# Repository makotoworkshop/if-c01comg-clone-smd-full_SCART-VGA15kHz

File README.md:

IF-C01COMG Clone board SMD Full size_SCART-VGA15kHz

This is a full sized version of the IF-C01COMG board for JVC pro monitors (TM-Hxx50CG) and some others...

It's basically the THT base board I made some months ago, with most components changed to SMD.

Credit goes to James Vanderloeff for the dual input idea.

Board is for now completely untested...

Finally this is a Kicad 5.1 project :D

You're welcome to clone, sell, re-design and whatever, see LICENSE.

(2021) Martin Hejnfelt (martin@hejnfelt.com)
This work is free. You can redistribute it and/or modify it under the
terms of the Do What The Fuck You Want To Public License, Version 2,
as published by Sam Hocevar. See the LICENSE file for more details.

—————————————————————————————

edit (2024) makotoworkshop.org

For more informations, see https://burogu.makotoworkshop.org/index.php?post/2024/08/08/jvc-rgb

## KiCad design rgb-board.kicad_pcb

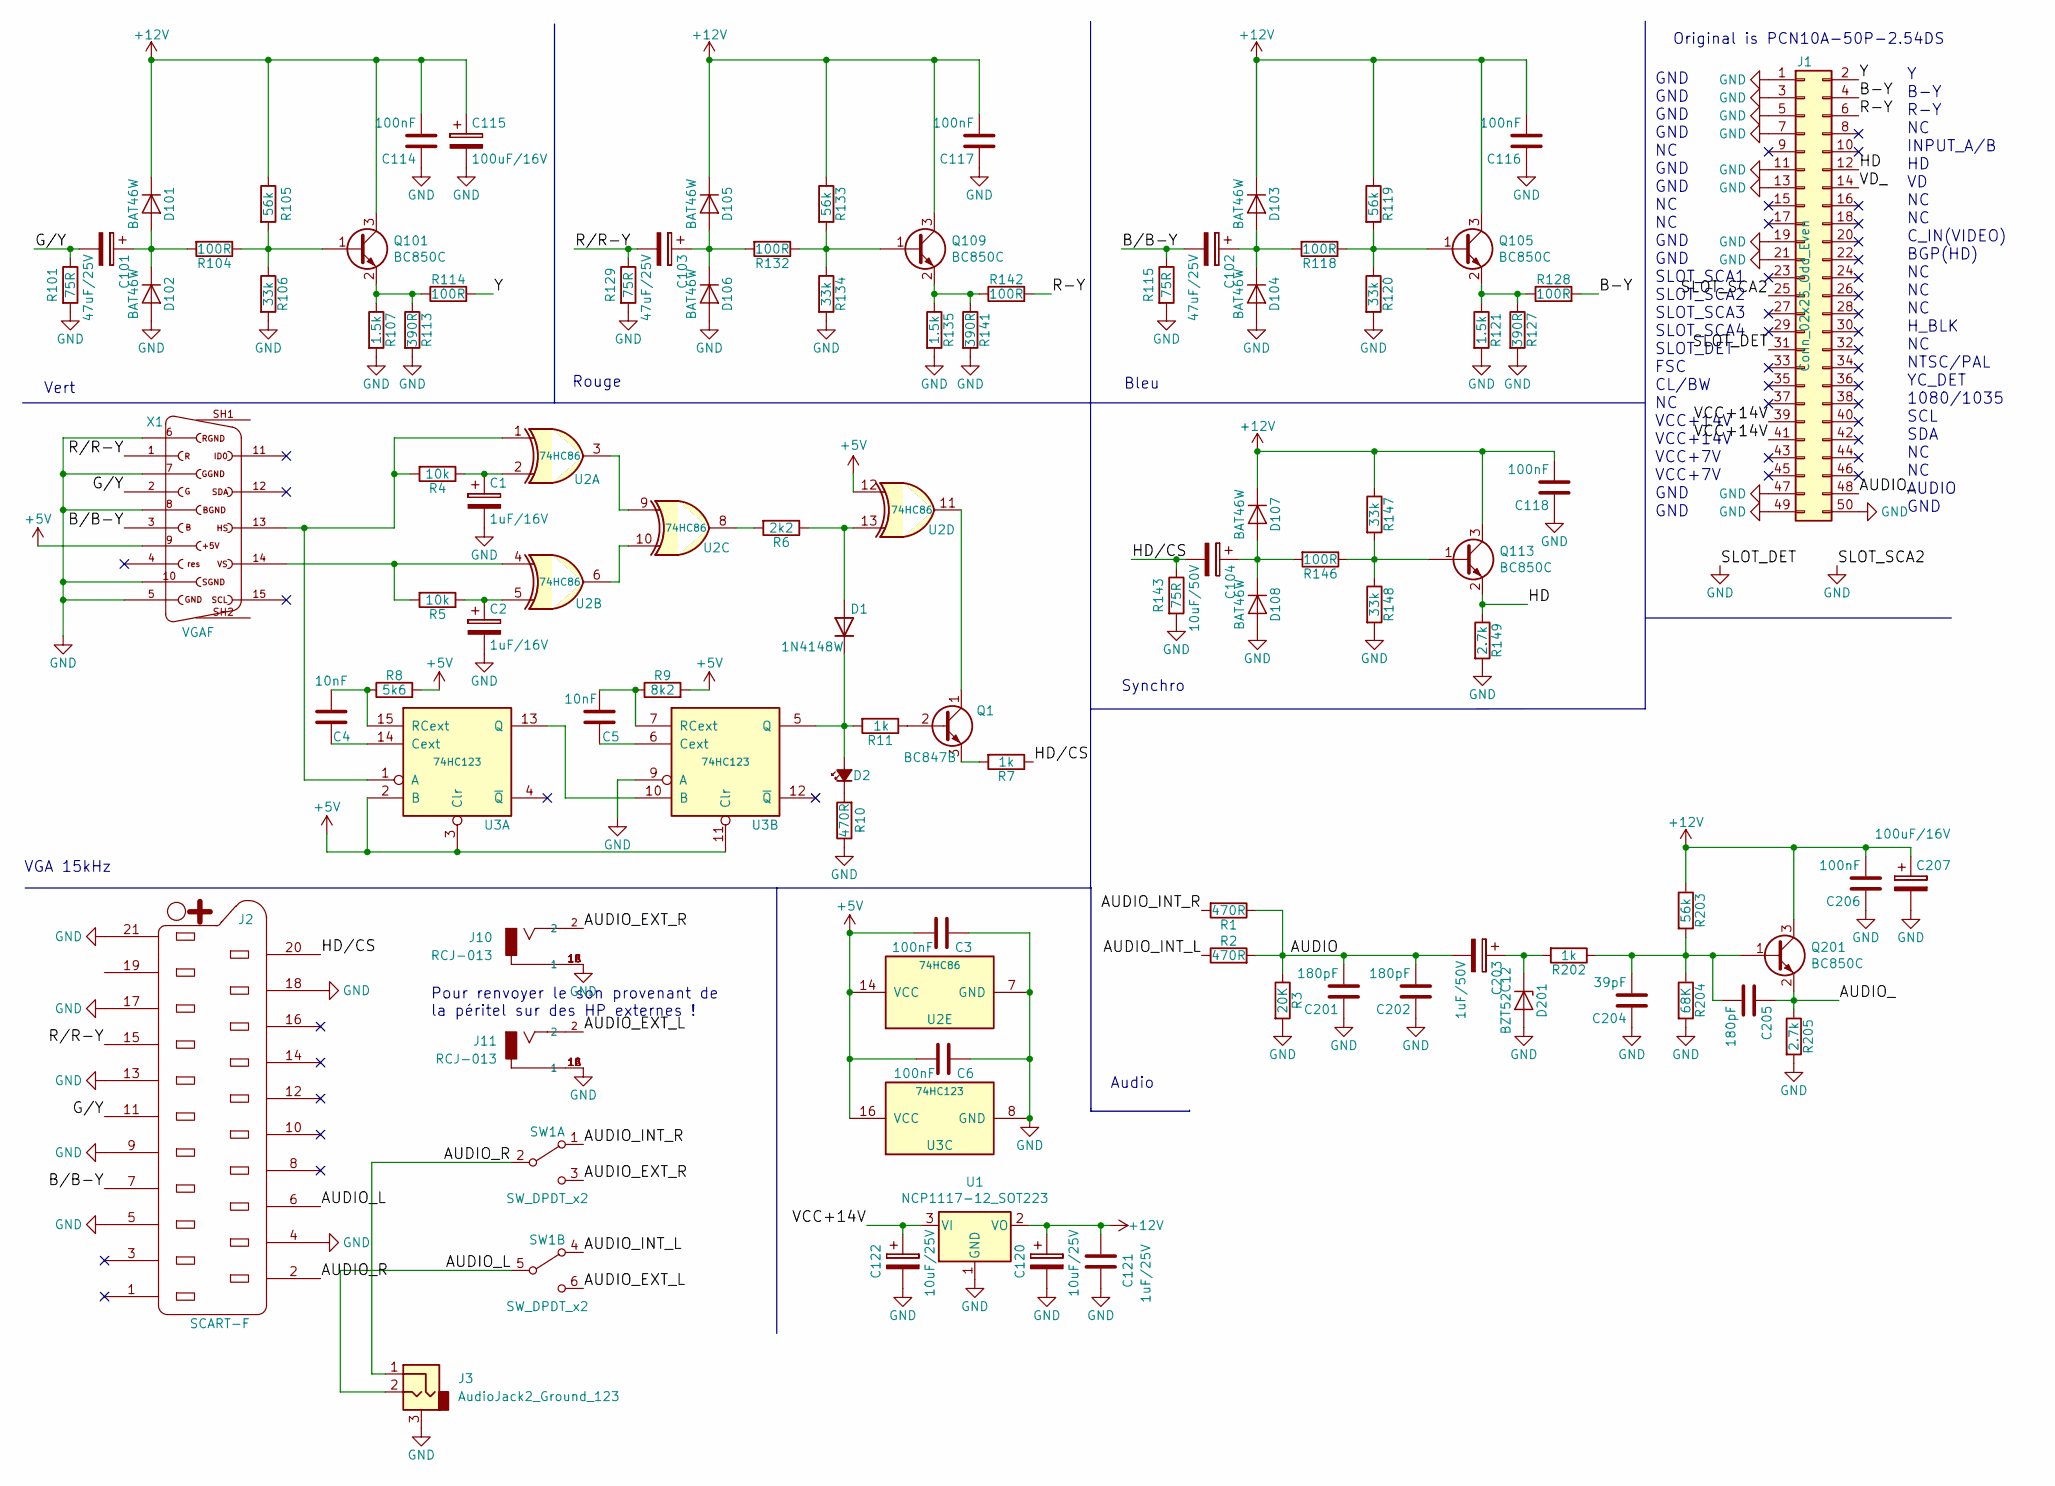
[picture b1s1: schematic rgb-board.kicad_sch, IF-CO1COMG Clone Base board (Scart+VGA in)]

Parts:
C1, C2: 1uF/16V; C_Elec_4x5.4
C3, C6, C114, C116, C117, C118, C206: 100nF; C_1206_3216Metric_Pad1.33x1.80mm_HandSolder
C4, C5: 10nF; C_1206_3216Metric_Pad1.33x1.80mm_HandSolder
C101, C102, C103: 47uF/25V; C_Elec_6.3x5.4
C104: 10uF/50V; C_Elec_5x5.4
C115, C207: 100uF/16V; C_Elec_6.3x5.4
C120, C122: 10uF/25V; C_Elec_4x5.4
C121: 1uF/25V; C_1206_3216Metric_Pad1.33x1.80mm_HandSolder
C201, C202, C205: 180pF; C_1206_3216Metric_Pad1.33x1.80mm_HandSolder
C203: 1uF/50V; C_Elec_4x5.4
C204: 39pF; C_1206_3216Metric_Pad1.33x1.80mm_HandSolder
D1: 1N4148W; D_SOD-123
D2: LED_Small_Filled; LED_D5.0mm_Horizontal_O1.27mm_Z3.0mm
D101, D102, D103, D104, D105, D106, D107, D108: BAT46W; D_SOD-123
D201: BZT52C12; D_SOD-123
J1: Conn_02x25_Odd_Even; Pin_Header_Angled_2x25_Pitch2.54mm
J2: SCART-F; NINIGI-SCART-RA
J3: AudioJack2_Ground_123; PinHeader_1x03_P2.54mm_Vertical
J10, J11: RCJ-013; CUI_RCJ-013; PART_REV B
Q1: BC847B; SOT-23_Handsoldering
Q101, Q105, Q109, Q113, Q201: BC850C; SOT-23_Handsoldering
R1, R2, R10: 470R; R_1206_3216Metric_Pad1.30x1.75mm_HandSolder
R3: 20K; R_1206_3216Metric_Pad1.30x1.75mm_HandSolder
R4, R5: 10k; R_1206_3216Metric_Pad1.30x1.75mm_HandSolder
R6: 2k2; R_1206_3216Metric_Pad1.30x1.75mm_HandSolder
R7, R11, R202: 1k; R_1206_3216Metric_Pad1.30x1.75mm_HandSolder
R8: 5k6; R_1206_3216Metric_Pad1.30x1.75mm_HandSolder
R9: 8k2; R_1206_3216Metric_Pad1.30x1.75mm_HandSolder
R101, R115, R129, R143: 75R; R_1206_3216Metric_Pad1.30x1.75mm_HandSolder
R104, R114, R118, R128, R132, R142, R146: 100R; R_1206_3216Metric_Pad1.30x1.75mm_HandSolder
R105, R119, R133, R203: 56k; R_1206_3216Metric_Pad1.30x1.75mm_HandSolder
R106, R120, R134, R147, R148: 33k; R_1206_3216Metric_Pad1.30x1.75mm_HandSolder
R107, R121, R135: 1.5k; R_1206_3216Metric_Pad1.30x1.75mm_HandSolder
R113, R127, R141: 390R; R_1206_3216Metric_Pad1.30x1.75mm_HandSolder
R149, R205: 2.7k; R_1206_3216Metric_Pad1.30x1.75mm_HandSolder
R204: 68K; R_1206_3216Metric_Pad1.30x1.75mm_HandSolder
SW1: SW_DPDT_x2; LC2259
U1: NCP1117-12_SOT223; SOT-223-3_TabPin2
U2: 74HC86; SOIC-14_3.9x8.7mm_P1.27mm
U3: 74HC123; SOIC-16_3.9x9.9mm_P1.27mm
X1: VGAF; HD15_B-HD15F

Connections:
+5V: C3.2, C6.2, R8.2, R9.2, U2.12, U2.14 (VCC), U3.2 (B), U3.3 (Clr), U3.11 (Clr), U3.16 (VCC), X1.9; also elsewhere on the board
+12V: C114.2, C115.1, C116.2, C117.2, C118.2, C120.1, C121.2, C206.2, C207.1, D101.1 (K), D103.1 (K), D105.1 (K), D107.1 (K), Q101.3 (C), Q105.3 (C), Q109.3 (C), Q113.3 (C), Q201.3 (C), R105.1, R119.1, R133.1, R147.1, R203.1, U1.2 (VO)
/AUDIO: C201.2, C202.2, C203.2, R1.1, R2.2, R3.1
/AUDIO_: C205.1, J1.48, Q201.2 (E), R205.1
/AUDIO_EXT_L: J11.2, SW1.6 (C)
/AUDIO_EXT_R: J10.2, SW1.3 (C)
/AUDIO_INT_L: R2.1, SW1.4 (A)
/AUDIO_INT_R: R1.2, SW1.1 (A)
/AUDIO_L: J2.6, J3.2, SW1.5 (B)
/AUDIO_R: J2.2, J3.1, SW1.2 (B)
/B-Y: J1.4, R128.2
/B/B-Y: C102.2, J2.7, R115.1, X1.3
/G/Y: C101.2, J2.11, R101.1, X1.2
/HD: J1.12, Q113.2 (E), R149.1
/HD/CS: C104.2, J2.20, R7.1, R143.1
/R-Y: J1.6, R142.2
/R/R-Y: C103.2, J2.15, R129.1, X1.1
/VCC+14V: C122.1, J1.39, J1.41, U1.3 (VI); also elsewhere on the board
/VD_: J1.14
/Y: J1.2, R114.2
GND: C1.2, C2.2, C3.1, C6.1, C114.1, C115.2, C116.1, C117.1, C118.1, C120.2, C121.1, C122.2, C201.1, C202.1, C204.1, C206.1, C207.2, D102.2 (A), D104.2 (A), D106.2 (A), D108.2 (A), D201.2 (A), J1.1, J1.3, J1.5, J1.7, J1.11, J1.13, J1.19, J1.21, J1.25, J1.31, J1.47, J1.49, J1.50, J2.4, J2.5, J2.9, J2.13, J2.17, J2.18, J2.21, J3.3, J10.1A (1), J10.1B (1), J10.1C (1), J11.1A (1), J11.1B (1), J11.1C (1), R3.2, R10.1, R101.2, R106.2, R107.2, R113.2, R115.2, R120.2, R121.2, R127.2, R129.2, R134.2, R135.2, R141.2, R143.2, R148.2, R149.2, R204.2, R205.2, U1.1 (GND), U2.7 (GND), U3.8 (GND), U3.9 (A), X1.5, X1.6, X1.7, X1.8, X1.10; also elsewhere on the board
unnamed: C1.1, R4.1, U2.2
unnamed: C2.1, R5.1, U2.5
unnamed: D1.2 (A), R6.1, U2.13
unnamed: D1.1 (K), D2.2 (A), R11.2, U3.5 (Q)
unnamed: D2.1 (K), R10.2
unnamed: C101.1, D101.2 (A), D102.1 (K), R104.2
unnamed: C102.1, D103.2 (A), D104.1 (K), R118.2
unnamed: C103.1, D105.2 (A), D106.1 (K), R132.2
unnamed: C104.1, D107.2 (A), D108.1 (K), R146.2
unnamed: C203.1, D201.1 (K), R202.2
unnamed: Q1.2 (B), R11.1
unnamed: Q1.1 (C), U2.11
unnamed: Q1.3 (E), R7.2
unnamed: Q101.1 (B), R104.1, R105.2, R106.1
unnamed: Q101.2 (E), R107.1, R113.1, R114.1
unnamed: Q105.1 (B), R118.1, R119.2, R120.1
unnamed: Q105.2 (E), R121.1, R127.1, R128.1
unnamed: Q109.1 (B), R132.1, R133.2, R134.1
unnamed: Q109.2 (E), R135.1, R141.1, R142.1
unnamed: Q113.1 (B), R146.1, R147.2, R148.1
unnamed: C204.2, C205.2, Q201.1 (B), R202.1, R203.2, R204.1
unnamed: R5.2, U2.4, X1.14
unnamed: R6.2, U2.8
unnamed: U2.3, U2.9
unnamed: U2.6, U2.10
unnamed: R4.2, U2.1, U3.1 (A), X1.13
unnamed: C4.1, U3.14 (Cext)
unnamed: U3.10 (B), U3.13 (Q)
unnamed: C4.2, R8.1, U3.15 (RCext)
unnamed: C5.2, U3.6 (Cext)
unnamed: C5.1, R9.1, U3.7 (RCext)

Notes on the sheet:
Bleu
Pour renvoyer le son provenant de la péritel sur des HP externes !
Vert
Original is PCN10A-50P-2.54DS
Synchro
Y B-Y R-Y NC INPUT_A/B HD VD NC NC C_IN(VIDEO) BGP(HD) NC NC NC H_BLK NC NTSC/PAL YC_DET 1080/1035 SCL SDA NC NC AUDIO GND
Audio
GND GND GND GND NC GND GND NC NC GND GND SLOT_SCA1 SLOT_SCA2 SLOT_SCA3 SLOT_SCA4 SLOT_DET FSC CL/BW NC VCC+14V VCC+14V VCC+7V VCC+7V GND GND
VGA 15kHz
Rouge

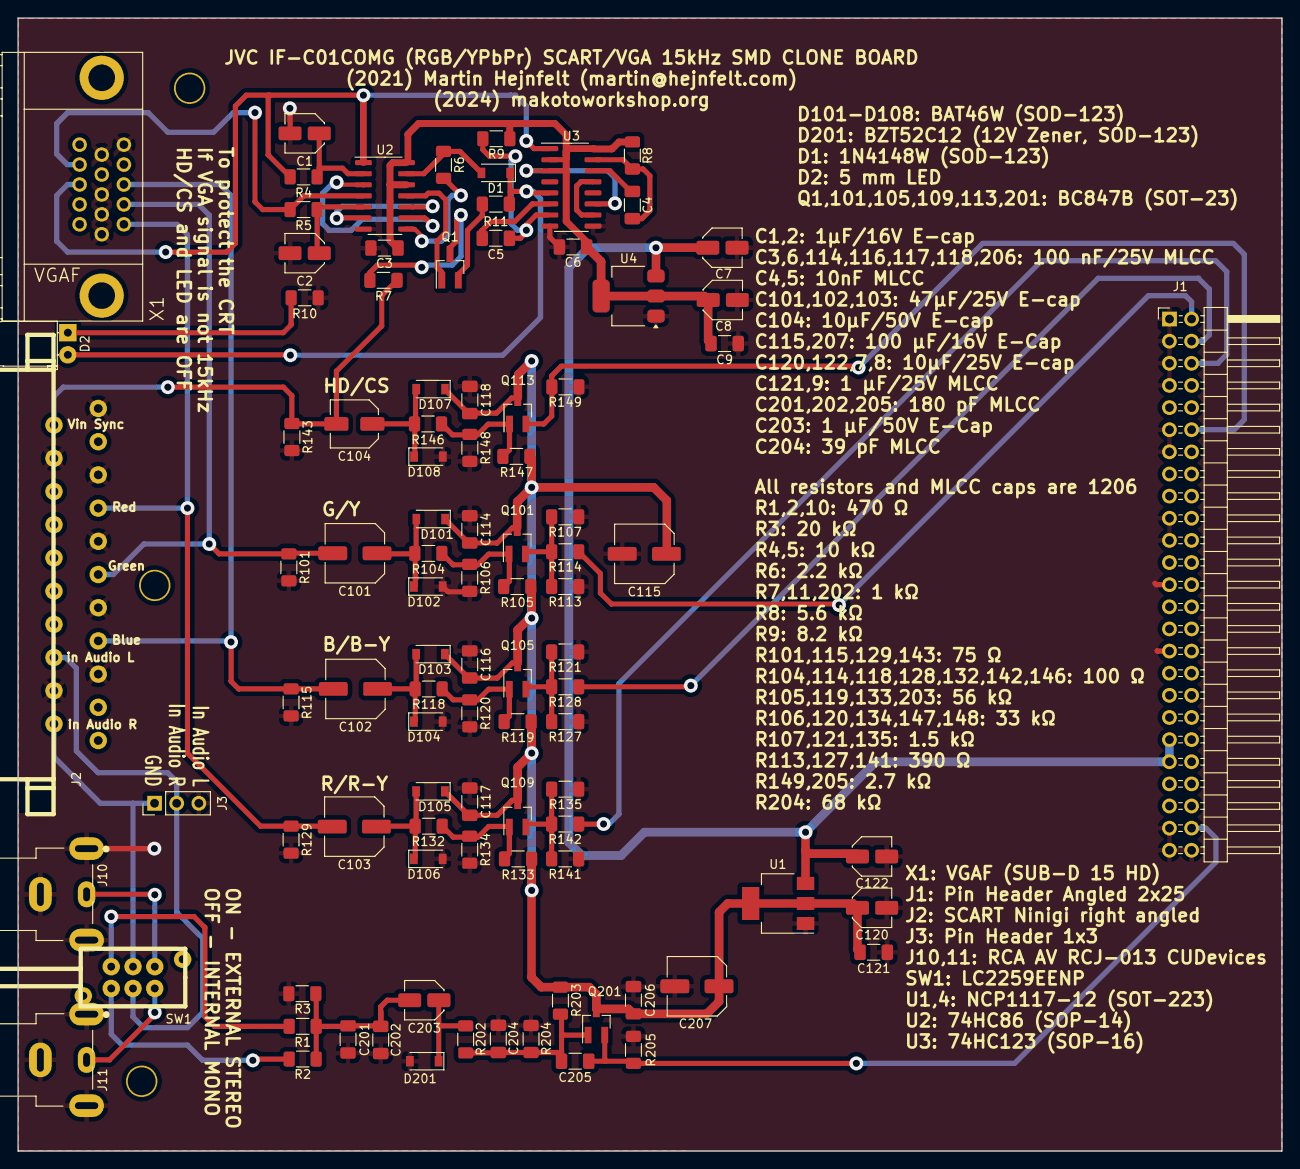
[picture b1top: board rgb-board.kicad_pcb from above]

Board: 2 copper layers, 145.0 x 130.0 mm, 100 parts (0 on the bottom side), 51 nets.

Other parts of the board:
C7, C8: 10uF/25V; C_Elec_4x5.4
C9: 1uF/25V; C_1206_3216Metric_Pad1.33x1.80mm_HandSolder
J4, J4#2, J4#3: TEST_1P; MountingHole_3.2mm_M3
U4: NCP1117-5_SOT223; SOT-223-3_TabPin2

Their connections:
+5V: C8.1, C9.2, U4.2 (VO); also elsewhere on the board
/VCC+14V: C7.1, U4.3 (VI); also elsewhere on the board
GND: C7.2, C8.2, C9.1, U4.1 (GND); also elsewhere on the board

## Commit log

2024-08-10 Create lib
2025-11-29 Update rgb-board.kicad_pro
    5V-corrigé
2025-11-29 Update rgb-board.kicad_pcb
    5V-corrigé
